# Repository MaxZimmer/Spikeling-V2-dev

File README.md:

# Spikeling V 2.0

Spikeling V2.0 is an educational tool for neuroscience students and enthusiasts!

<p style='text-align: justify;'>
It is an artificial neuron that can receive different inputs, integrate them and send and outputs its computation, just like a spiking neuron would!

Technically, it consists on a microcontroller (an ESP32) running the computationally efficient Izhikevich model of a spiking neuron.
</p>

This project is licensed under the [GNU General Public License v3.0](https://github.com/BadenLab/Openspritzer/blob/master/LICENSE)<br>
The hardware is licensed under the [CERN OHL v1.2](https://github.com/BadenLab/LED-Zappelin/blob/master/PCB/LICENSE)

<br>

<div>

</div>

<br>

<div>
<p style='text-align: justify;'>
If this all sounds familiar to you, it is because this project is a derivative (and update) of the Spikeling project started at the <a href="https://badenlab.org">BadenLab</a>.
With feedback from users and students, we are developing this version, which has added capabilities, and also revisits how lessons can be taught, and what kind of experiments can be done with it!

While this is not a stable version just yet, enthusiasts and potential collaborators can source the electronic bits for this project from <a href="https://kitspace.org/boards/github.com/maxzimmer/spikeling-v2/">KitSpace</a></p>
</div>

***

<div>
<p style='text-align: justify;'>

<p style='text-align: justify;'>
The main upgrade on the PCB concerns the use of an ESP32 module and 2 ADC 8bit expander chips that together allow spikeling to compute more input output with specific input/output ports and dedicated potentiometer. The previous version had limited ports and potentiometers and different functions had to be encoded on the arduino code hence impacting the versatility of the model.

Stereo (3-ways) audio jacks 3.5mm replace the previous BNC cable. Both ports and cables are therefore cheaper, also ports are less bulky and cables more flexible. Moreover, now one single port can carry two distinct information. In this case digital and analog input/output.

Since the user cannot access the microcontroler board anymore (acrylic sheet on top of the board), a reset button has been added to the back of the board.

Previously, "modes" were encoded manually on the microcontroler, and the user could check the set mode number by the amount of flashes the microcontroller built-in LED was providing at the begining of the routine.
Now, the microcontroller is pre-set with 12 distinct "neuron modes" that the user can switch through, 12 proxy LED indicate continuously which mode is currently being set.

The buzzer is now smaller and is powered by the ESP32 3.3V (instead of the 5v from the arduino), making its clicking noise quieter, which is more pleasant for the user ear, especially after a couple of minutes using the device.

A couple of functions have been added to the board and can now be controlled through potentiometers (synaptic polarity(inhibitory/excitatory), photoreceptor gain and polarity, stimulus strength and polarity(only for current input not LED stimulation)).

Another major upgrade concerns the use of the two DAC GPIO from the ESP32. These two are conencted to the synapse out analog, which can be read either by another Spikeling synaptic in analog input port, or either by an external oscilloscope. The other DAC port is connected to the stimulus analog out, whcich drives the Current-in port (from the patch clamp module), therefore improving the direct stimulation from the board.

</p>
</div>

***

<div>

<p style='text-align: justify;'>

The entire layout of the Spikeling board has been reconceived and a laser-cut acrylic sheet repesenting a neuron now sit on top of the board. All ports and potentiometers are now strategically placed.

The ESP32 is placed below the soma, the synaptic inputs from other Spikeling units are placed on the left, the synaptic output is placed on the right. Along the axon now sits a RGB LED, the red LED brightness follows as before the Vm status of the neuron, and the LED sparks in white when the neuron spike. The spike buzzer also sit along the axon, a small hole on the acrylic sheet sitting just above so the click can be heard coming from that direction.

The Vm potentiometer and the Current-in port are now grouped together and sit on the acrylic sheet at the bottom of an electrode pipette. They can now be considered as a voltage clamp experiment variables.

A photoreceptor is now drawn on the acrylic sheet, below the opsin sits a photodiode, and a potentiometer on the photoreceptor body now controls the photoreceptor sensitivity and its polarity (the user decides then if the PR has an excitatory or an inhibitory effect on the neuron)

The noise potentiometer now sits in a box by itself as it represents parasitic noise from the experiment environment and is independent from the rest of the Spikeling functions. This potentiometer is different from the others as it is not center-detented as it generates noise from a zero to a maximum value.

Next is the Neuron mode box which contains the 12 available modes to the users and a push button that allows the user to switch between them.

Finally, the last box contains all experimental tools allowing stimuli generation. As detailled on the acrylic sheet, the user can control the stimulus frequency and the stimulus strenght, along with its polarity. The stimulus output can either be directly connected to the current in port to simulate a current applied to a voltage held neuron through the pipette. Or be connected to a cable with a 5mm LED soldered at its tip which can be placed directly on top of the photoreceptor opsin (photodiode below). The photoreceptor possesses functions (decay/recovery) simulating how a real photoreceptor would integrate a light stimuli and how it will adapt to prolonged stimulation.  

</p>
</div>

***

<div>

<p style='text-align: justify;'>

Spikeling now possesses its own GUI, written in python and using the latest pyQt6 library. The script then uses pyInstall so it can be translated into a desktop app, ready to be easily distributed to users.

The GUI is divided (for the moment) into distinct tabs. The first one is the main GUI window where the user connects the board to the computer, can choose to either select the neuron mode on the board directly or through the GUI (note that custom modes will have to be selected from here, and in this instance the GUI takes priority over the board commands).

The main window display the Spikeling activity (Neuron Vm, total current input from all sources & stimulus state). If connected to other spikeling, the GUI can display fore both synaptic input, their incoming neuron Vm and their spiking event, which will be translated into input current for the main neuron. Traces can be selected through checkbox and superimposed over the same graph with a common timeline.

Below the main window, Spikeling traces can be recorded either live or for only a fixed amount of stimulation loop.

On the right hand side two control columns can be found. For all commands, when the checkbox is clicked, the GUI takes over the potentiometer and controls directly the Spikeling variable. This allow advanced user to finely design an experimental protocol for example.

Below the stimulus frequency and strength sliders can be found a custom stimulus display. Here the user can choose to use instead of the classical square wave, either a stimulus from a pre-design library (comprising sine wave, chirp, white noise, etc.), or either a custom made stimulus generated from the GUI "stimulus generator" tab.

One the first Spikeling version, if the user wanted to change the set variable for the photoreceptor and synaptic set variable (gain, decay, recovery, polarity, etc.), one had to manually reupload the arduino code with these changes, and no proper experimental protocol could be establish. Here by clicking the checkbox, the user had the opportunity to change these value directly and therefore is able to play further with each Spikeling parameter, opening the way for teacher to come up with their own personal exercises.

</p>
</div>

***

<div>

<p style='text-align: justify;'>

In this tab, the user can play directly with the Izhikevich model. A short text from Izhikevich publications explain the role of each variable (later upgrade will include hyperlink to these publication along with pop up window detailing further what the code is actually doing).

The main window computes the code with a current input of +15 (as in Izhikevich publication). User can change the 4 variable of the code and display the resulting "neuron mode". This is also where user can come up with its own neuronal modes to experiment on if the 12 pre-set one are not enough. This is also where teachers can generate their own custom made neuron, save them, and impose them as experimental model for i.e. homework exercises.

</p>
</div>

***

Stimulus generator and data analysis tabs needs to be finished (cf. development log) but they will include ... a stimulus generator, allowing the user to come up with custom made stimulation loop, and ... a data analysis routine for early computation course where student could upload their recorded traces and extract information from it, generating raster plot, computing data and generate basic statistics. For advanced courses an integrated python exercise manual (no IGOR !!!) will guide students through creating a data analysis pipeline using .csv files saved from the main window.

<br>
<div>

# Development log

### Working Issues

##### Arduino

The negative photogain does not decay towards zero, an absolute value has to be implemented

##### GUI

- Serial reading is slow and pyQtgraph does not update fast enough the serial values.

>FIXED: The entire code was reimplement using a lower BaudRate (9600 instead of 115200) and the pyQtgraph routine was improved.
Currently the GUI functions are being reimplemented with the PySerial readWrite functions. Updates to come.

##### PCB

- The audio jack footprint is not correct. the back pin and holes are mm ahead of their correct position.

>FIXED: the new PCB in the 2.2c version now posses the correct footprint. Previous version will need to cut the plastic pieces in front of the audio jack female and force the component into position

- The LEDs on the board might be to Bright

> The resistance of the 4 CharliePlex and the SpikeLed resistors must be adjusted to the acrylic material chosen for the front cover. The current 100 Ohm is sufficient for opaque PMMA, but clear transparent ones should have 1 kOhm soldered below so that the LEDs do not affect the user vision.

- The CharliePlex footprint orientation (+/-) is not labeled

- Stimulus generation tab to be reimplemented

- Data Analysis tab to be reimplemented

- About tab to be created

##### Acrylic sheet

The custom 1, 2, 3 text has to be changed to the last three neuron mode implemented on the arduino code

> FIXED

</div>

***

Cost estimation spreadsheet for production
https://docs.google.com/spreadsheets/d/1JO1rpfb5DoqT5x59RL3RnkQFxRdzm5al6X8uEcsVFo8/edit#gid=0

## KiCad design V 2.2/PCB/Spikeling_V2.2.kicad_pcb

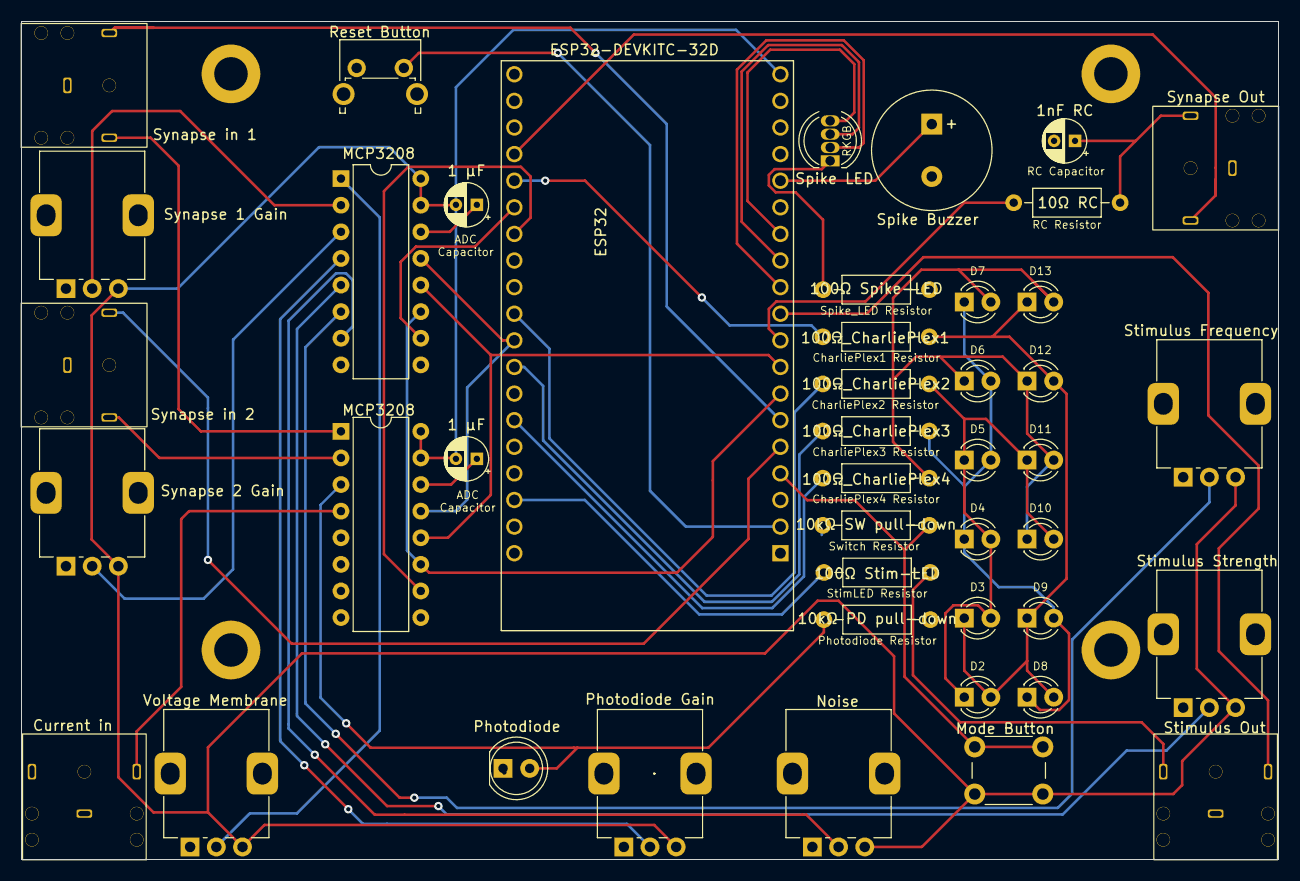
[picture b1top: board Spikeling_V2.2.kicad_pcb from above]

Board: 2 copper layers, 120.0 x 80.0 mm, 50 parts (0 on the bottom side), 41 nets.

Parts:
 : MountingHole_3.2mm_M3_DIN965_Pad
 #2: MountingHole_M3; MountingHole_3.2mm_M3_DIN965_Pad
 #3,  #4: MountingHole_3.2mm_M3_DIN965_Pad
.: Spikeling_neuron; Spikeling_Photoreceptor
BZ1: Spike Buzzer; Buzzer_11.5x9.5RM5
C1, C2: 1 μF; CP_Radial_D4.0mm_P2.00mm
C3: 1nF RC; CP_Radial_D4.0mm_P2.00mm
D1: Photodiode; LED_D5.0mm
D2: Mode1; LED_D3.0mm
D3: Mode2; LED_D3.0mm
D4: Mode3; LED_D3.0mm
D5: Mode4; LED_D3.0mm
D6: Mode5; LED_D3.0mm
D7: Mode6; LED_D3.0mm
D8: Mode7; LED_D3.0mm
D9: Mode8; LED_D3.0mm
D10: Mode9; LED_D3.0mm
D11: Mode10; LED_D3.0mm
D12: Mode11; LED_D3.0mm
D13: Mode12; LED_D3.0mm
D14: Spike LED; LED_D5.0mm-4_RGB
ESP32: Spikeling_neuron; Spikeling_Neuron
J1: Synapse Out; Spikeling Audio Jack 3.5mm
J2: Synapse in 1; Spikeling Audio Jack 3.5mm
J3: Synapse in 2; Spikeling Audio Jack 3.5mm
J4: Current in; Spikeling Audio Jack 3.5mm
J5: Stimulus Out; Spikeling Audio Jack 3.5mm
R1: 10Ω RC; R_Axial_DIN0207_L6.3mm_D2.5mm_P10.16mm_Horizontal
R2: 10kΩ PD pull-down; R_Axial_DIN0207_L6.3mm_D2.5mm_P10.16mm_Horizontal
R3: 100Ω Stim-LED; R_Axial_DIN0207_L6.3mm_D2.5mm_P10.16mm_Horizontal
R4: 100Ω Spike-LED; R_Axial_DIN0207_L6.3mm_D2.5mm_P10.16mm_Horizontal
R5: 10kΩ SW pull-down; R_Axial_DIN0207_L6.3mm_D2.5mm_P10.16mm_Horizontal
R6: 100Ω_CharliePlex1; R_Axial_DIN0207_L6.3mm_D2.5mm_P10.16mm_Horizontal
R7: 100Ω_CharliePlex2; R_Axial_DIN0207_L6.3mm_D2.5mm_P10.16mm_Horizontal
R8: 100Ω_CharliePlex3; R_Axial_DIN0207_L6.3mm_D2.5mm_P10.16mm_Horizontal
R9: 100Ω_CharliePlex4; R_Axial_DIN0207_L6.3mm_D2.5mm_P10.16mm_Horizontal
RV1: Synapse 1 Gain; Spikeling Potentiometer
RV2: Synapse 2 Gain; Spikeling Potentiometer
RV3: Voltage Membrane; Spikeling Potentiometer
RV4: Noise; Spikeling Potentiometer
RV5: Photodiode Gain; Spikeling Potentiometer
RV6: Stimulus Strength; Spikeling Potentiometer
RV7: Stimulus Frequency; Spikeling Potentiometer
SW1: Mode Button; SW_PUSH_6mm_H13mm
SW2: Reset Button; Spikeling reset button
U1: ESP32-DEVKITC-32D; MODULE_ESP32-DEVKITC-32D
U2, U3: MCP3208; DIP-16_W7.62mm

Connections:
/00: U1.33 (IO0), U2.10 (~CS/SHDN)
/02: R6.1, U1.34 (IO2)
/04: U1.32 (IO4), U3.10 (~CS/SHDN)
/05: R7.1, U1.29 (IO5)
/12: D14.4 (BA), U1.13 (IO12)
/13: BZ1.1 (-), U1.15 (IO13)
/14: D14.3 (GA), U1.12 (IO14)
/15: J1.T, U1.35 (IO15)
/18: U1.28 (IO18), U2.13 (CLK), U3.13 (CLK)
/19: R8.1, U1.27 (IO19)
/21: R9.1, U1.25 (IO21)
/22: R3.1, U1.22 (IO22)
/25: R1.1, U1.9 (IO25)
/26: J5.R, U1.10 (IO26)
/27: D14.1 (RA), U1.11 (IO27)
/32: U1.7 (IO32), U2.11 (Din), U3.11 (Din)
/33: U1.8 (IO33), U2.12 (Dout), U3.12 (Dout)
/34: J3.T, U1.5 (IO34)
/35: J2.T, U1.6 (IO35)
/39: R5.1, SW1.1, U1.4 (SENSOR_VN)
/100: RV3.2, U2.1 (CH0)
/101: RV1.2, U2.2 (CH1)
/102: RV2.2, U2.3 (CH2)
/103: RV5.2, U2.4 (CH3)
/104: RV6.2, U2.5 (CH4)
/105: RV7.2, U2.6 (CH5)
/106: RV4.2, U2.7 (CH6)
/200: J2.R, U3.1 (CH0)
/201: J3.R, U3.2 (CH1)
/202: D1.2 (A), R2.1, U3.3 (CH2)
/203: J4.R, U3.4 (CH3)
GNDREF: BZ1.2 (+), C1.1, C2.1, C3.2, D1.1 (K), J1.S, J2.S, J3.S, J4.S, J5.S, R2.2, R4.1, R5.2, RV1.1, RV2.1, RV3.1, RV4.1, RV5.1, RV6.1, RV7.1, SW2.1, U1.14 (GND1), U1.20 (GND3), U1.26 (GND2), U2.9 (DGND), U2.14 (AGND), U3.9 (DGND), U3.14 (AGND)
unnamed: C3.1, J1.R, R1.2
unnamed: J5.T, R3.2
unnamed: D14.2 (K), R4.2
unnamed: D2.2 (A), D3.1 (K), D8.2 (A), D9.1 (K), D12.2 (A), D13.1 (K), R6.2
unnamed: D2.1 (K), D3.2 (A), D4.2 (A), D5.1 (K), D10.2 (A), D11.1 (K), R7.2
unnamed: D4.1 (K), D5.2 (A), D6.2 (A), D7.1 (K), D8.1 (K), D9.2 (A), R8.2
unnamed: D6.1 (K), D7.2 (A), D10.1 (K), D11.2 (A), D12.1 (K), D13.2 (A), R9.2
unnamed: SW2.2, U1.2 (EN)
VCC: C1.2, C2.2, RV1.3, RV2.3, RV3.3, RV4.3, RV5.3, RV6.3, RV7.3, SW1.2, U1.19 (EXT_5V), U2.15 (Vref), U2.16 (Vdd), U3.15 (Vref), U3.16 (Vdd)

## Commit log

2022-07-30 First Upload
2022-07-30 Update PCB
2022-07-30 Update Arduino
2022-07-30 Update LaserCut
2022-09-19 quick update
2022-09-19 code update
2022-09-20 general update
2022-09-22 pcb update
2022-10-03 reordering versions
2022-10-05 prepare for kitspace and restructure repo
2022-10-16 Create GUI folder
2022-10-16 Rearanging verision folders
2022-10-17 update GUI
2022-10-21 update Design
2022-10-21 update pictures
2022-10-21 update Images
2022-10-21 update PCB - audio jack fixed
2022-10-24 update image
2022-10-29 update Arduino code
2022-12-08 add a gitignore and code to detect serial properly in linux
2022-12-08 add cache and pyc files to gitignore
2022-12-09 removing building app folder
2023-01-14 update gitignore, clean up import calls, make dist one file
2023-01-15 add information about library dependencies arduino
2023-01-25 GUI reupload
2023-01-25 remove build folder
2023-02-24 GUI ploting fixed
2023-03-05 update GUI - serial issue fixed
